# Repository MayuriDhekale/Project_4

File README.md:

# Project_4
<br>
<b>Ultra High Speed Black Box Event Recorder</b>
 <br>
A compact, crash-resistant flight recorder built to capture and protect critical telemetry data at lightning-fast speeds during flight. The entire layout uses a solid copper ground plane and short signal paths to shield sensitive components from motor noise, all packed into a rugged, corner-mounted board shape optimized for maximum survivability.

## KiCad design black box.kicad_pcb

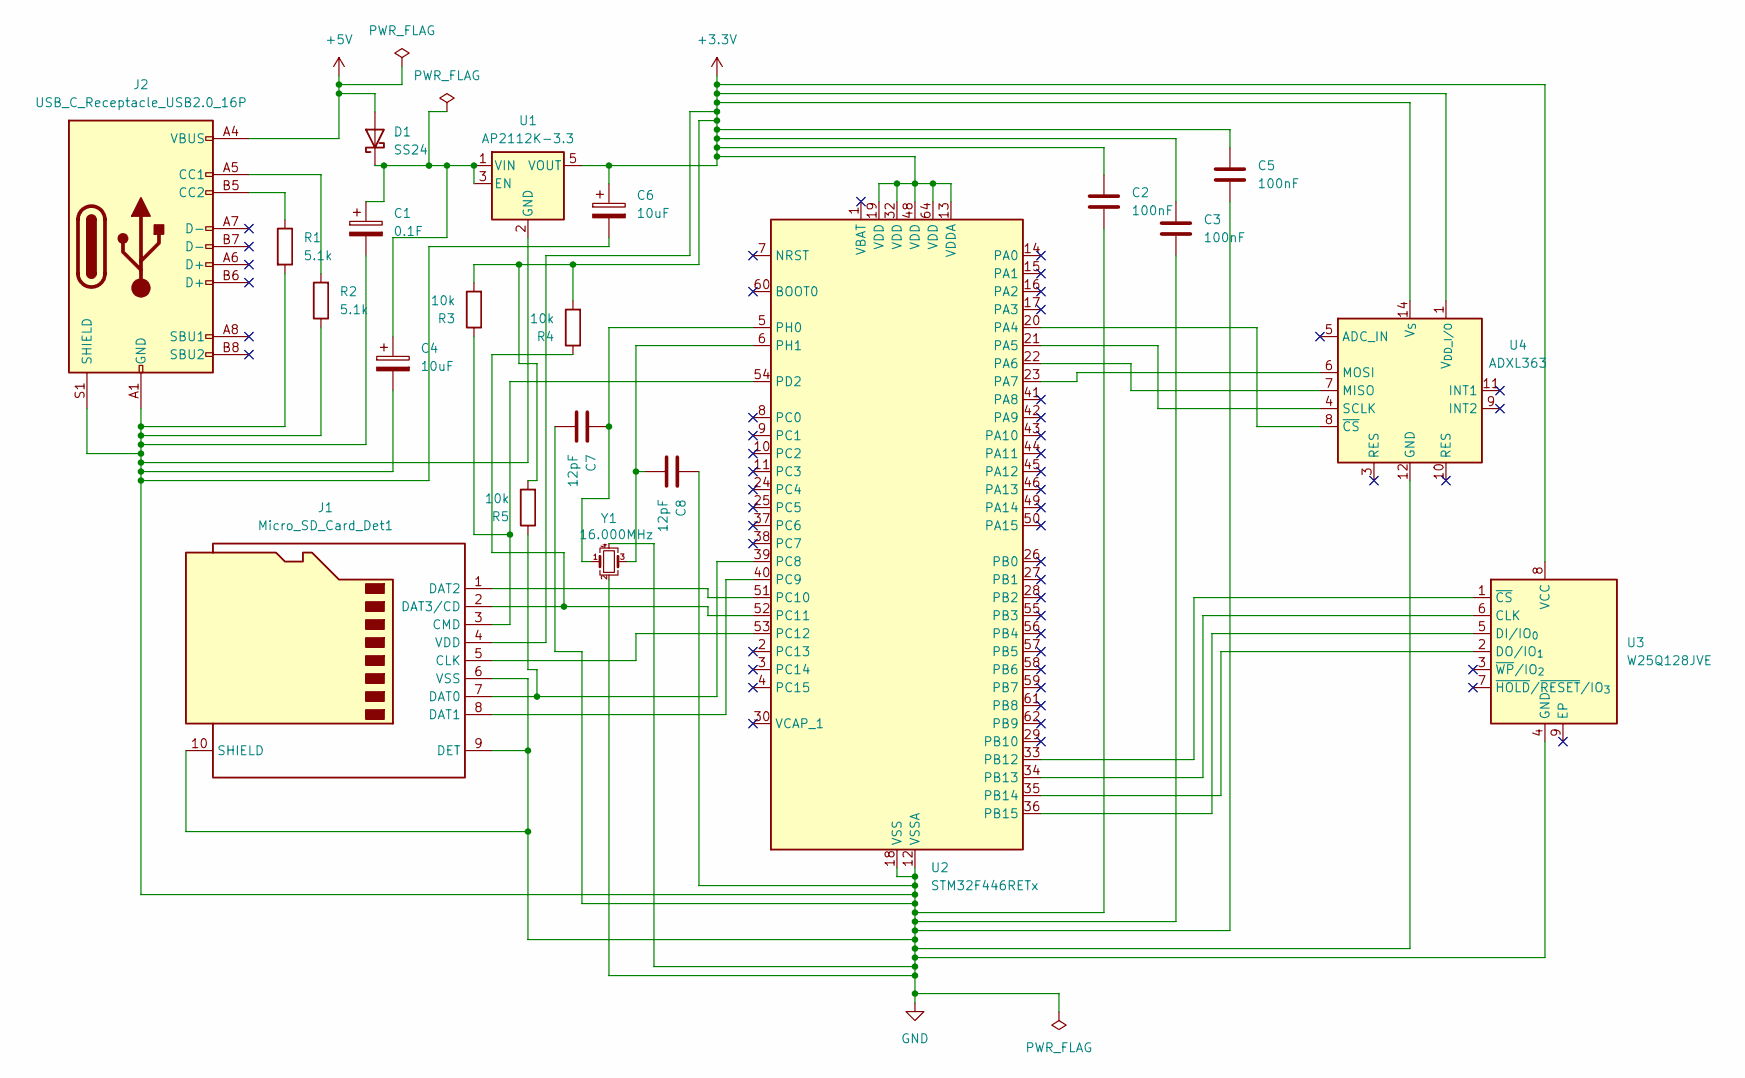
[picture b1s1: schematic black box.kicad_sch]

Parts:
C1: 0.1F; CP_Radial_D10.0mm_P5.00mm
C2, C3, C5: 100nF; C_0603_1608Metric
C4, C6: 10uF; C_0805_2012Metric
C7, C8: 12pF; C_0603_1608Metric
D1: SS24; D_SOD-123F
J1: Micro_SD_Card_Det1; microSD_HC_Molex_104031-0811
J2: USB_C_Receptacle_USB2.0_16P; USB_C_Receptacle_Palconn_UTC16-G
R1, R2: 5.1k; R_0603_1608Metric
R3, R4, R5: 10k; R_0603_1608Metric
U1: AP2112K-3.3; SOT-23-5
U2: STM32F446RETx; LQFP-64_10x10mm_P0.5mm
U3: W25Q128JVE; WSON-8-1EP_8x6mm_P1.27mm_EP3.4x4.3mm
U4: ADXL363; LGA-16_3x3mm_P0.5mm
Y1: 16.000MHz; Crystal_SMD_3225-4Pin_3.2x2.5mm

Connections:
+3.3V: C2.1, C3.2, C5.2, C6.1, J1.4 (VDD), R3.2, R4.2, R5.2, U1.5 (VOUT), U2.13 (VDDA), U2.19 (VDD), U2.32 (VDD), U2.48 (VDD), U2.64 (VDD), U3.8 (VCC), U4.1 (V_{DD_I/O}), U4.14 (V_{S})
+5V: D1.2 (A), J2.A4 (VBUS), J2.A9 (VBUS), J2.B4 (VBUS), J2.B9 (VBUS)
GND: C1.2, C2.2, C3.1, C4.2, C5.1, C6.2, C7.2, C8.1, J1.6 (VSS), J1.9 (DET), J1.10 (SHIELD), J2.A1 (GND), J2.A12 (GND), J2.B1 (GND), J2.B12 (GND), J2.S1 (SHIELD), R1.2, R2.1, U1.2 (GND), U2.12 (VSSA), U2.18 (VSS), U2.31 (VSS), U2.47 (VSS), U2.63 (VSS), U3.4 (GND), U4.12 (GND), U4.13 (GND), U4.16 (GND), Y1.2, Y1.4
unnamed: C1.1, C4.1, D1.1 (K), U1.1 (VIN), U1.3 (EN)
unnamed: J1.5 (CLK), U2.53 (PC12)
unnamed: J1.3 (CMD), R3.1, U2.54 (PD2)
unnamed: J1.7 (DAT0), R5.1, U2.39 (PC8)
unnamed: J1.8 (DAT1), U2.40 (PC9)
unnamed: J1.1 (DAT2), U2.51 (PC10)
unnamed: J1.2 (DAT3/CD), R4.1, U2.52 (PC11)
unnamed: J2.A5 (CC1), R2.2
unnamed: J2.B5 (CC2), R1.1
unnamed: U2.20 (PA4), U4.8 (~CS)
unnamed: U2.21 (PA5), U4.4 (SCLK)
unnamed: U2.22 (PA6), U4.7 (MISO)
unnamed: U2.23 (PA7), U4.6 (MOSI)
unnamed: U2.33 (PB12), U3.1 (~CS)
unnamed: U2.34 (PB13), U3.6 (CLK)
unnamed: U2.35 (PB14), U3.2 (DO/IO_{1})
unnamed: U2.36 (PB15), U3.5 (DI/IO_{0})
unnamed: C7.1, U2.5 (PH0), Y1.1
unnamed: C8.2, U2.6 (PH1), Y1.3

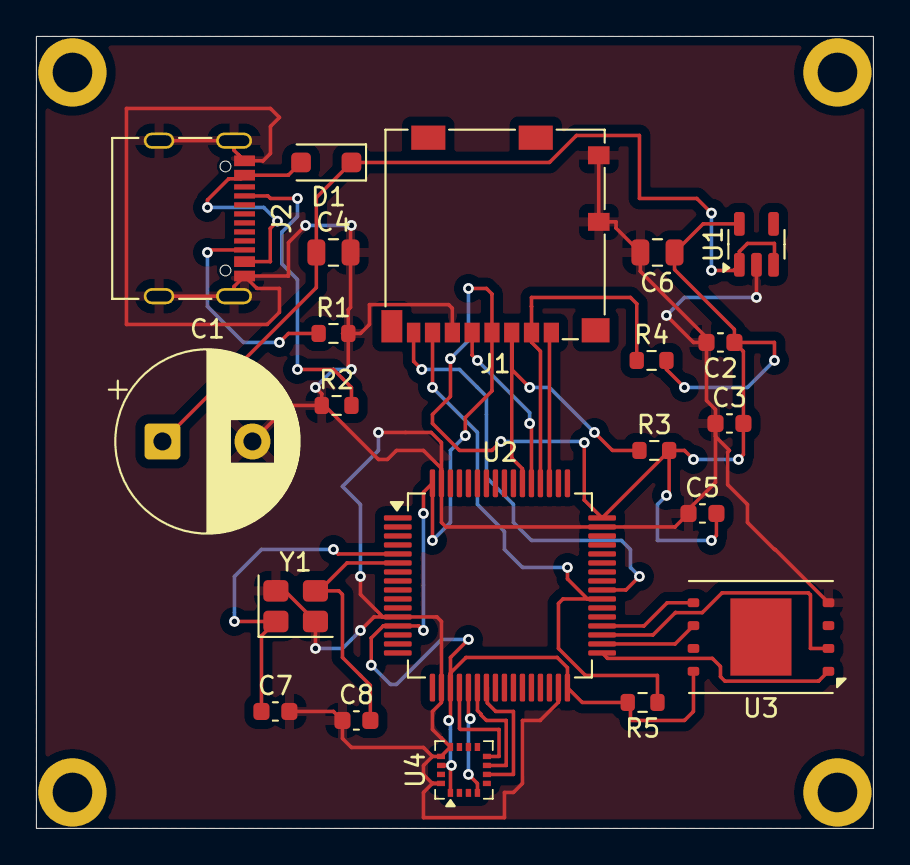
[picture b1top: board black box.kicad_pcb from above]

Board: 4 copper layers, 46.5 x 44.0 mm, 21 parts (0 on the bottom side), 22 nets.
